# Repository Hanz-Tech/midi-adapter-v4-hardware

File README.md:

Buy it Here 

OR

# Disclaimer

You are free to:

Share — copy and redistribute the material in any medium or format

Adapt — remix, transform, and build upon the material

________________________________________

Attribution — You must give appropriate credit, provide a link to the license, and indicate if changes were made. You may do so in any reasonable manner, but not in any way that suggests the licensor endorses you or your use.

NonCommercial — You may not use the material for commercial purposes.

___________________________________________

THE HARDWARE IS PROVIDED "AS IS", WITHOUT WARRANTY OF ANY KIND, EXPRESS OR IMPLIED, INCLUDING BUT NOT LIMITED TO THE WARRANTIES OF MERCHANTABILITY, FITNESS FOR A PARTICULAR PURPOSE AND NONINFRINGEMENT. IN NO EVENT SHALL THE AUTHORS OR COPYRIGHT HOLDERS BE LIABLE FOR ANY CLAIM, DAMAGES OR OTHER LIABILITY, WHETHER IN AN ACTION OF CONTRACT, TORT OR OTHERWISE, ARISING FROM, OUT OF OR IN CONNECTION WITH THE HARDWARE OR THE USE OR OTHER DEALINGS IN THE HARDWARE.

_____________________________________________

# Overview

This repo contains both the CAD for the 3D printed cover for the Pocket Operator and the PCB schematic for the adapter. PCB is created using KiCad. Software can be found [here](https://github.com/PO-MIDI-Adapter/midi-adapter-software/tree/v2)

## For assmebly instruction please go to the [wiki](https://github.com/PO-MIDI-Adapter/midi-adapter-hardware/wiki)

# Photos

# BOM
<!-- 
1. 1 x PCB board
2. 1 x 3D printed cover (Found in the cad folder)
3. 2 x cover holders  (Found in the cad folder)
4. 25 x pogo pins [ebay](https://www.ebay.ca/itm/100pcs-9mm-Length-Spring-Loaded-Test-Probes-Pogo-Pins-Cusp-Spear-for-Testing/163156710143?ssPageName=STRK%3AMEBIDX%3AIT&_trksid=p2057872.m2749.l46252)
5. 1 x PJ320B 3.5MM Audio Jack (ebay)

In addition, you would need the following electronics from Digikey (bom.csv)

|Manufacturer Part Number|Manufacturer               |Digi-Key Part Number|Quantity|Description                     |Placement|
|------------------------|---------------------------|--------------------|--------|--------------------------------|---------|
|SN74HC125N              |Texas Instruments          |296-1572-5-ND       |1       |IC BUFFER NON-INVERT 6V 14DIP   |U2
|A 14-LC-TT              |Assmann WSW Components     |AE9989-ND           |1       |CONN IC DIP SOCKET 14POS TIN    |U2
|1-2199298-1             |TE Connectivity            |A120346-ND          |1       |CONN IC DIP SOCKET 6POS TIN     |U3
|H11L1M                  |ON Semiconductors          |H11L1-MQT-ND        |1       |OPTOISO 4.17KV OPN COLL 6DIP    |U3
|PRPC028SACN-RC          |Sullins Connector Solutions|S1131EC-28-ND       |2       |CONN HEADER VERT 28POS 2.54MM   |U1
|DEV-16771               |SparkFun Electronics       |1568-DEV-16771-ND   |1       |TEENSY 4.1 W/OUT HDRS K66 EVAL  |U1
|SDS-50J                 |CUI Inc.                   |CP-2350-ND          |2       |CONN RCPT FMALE DIN 5POS SOLDER |J29,J30
|CF14JT220R              |Stackpole Electronics Inc  |CF14JT220RCT-ND     |3       |RES 220 OHM 1/4W 5% AXIAL       |R2,R3,R7
|CF14JT10K0              |Stackpole Electronics Inc  |CF14JT10K0CT-ND     |1       |RES 10K OHM 1/4W 5% AXIAL       |R4
|CF14JT470R              |Stackpole Electronics Inc  |CF14JT470RTR-ND     |1       |RES 470 OHM 1/4W 5% AXIAL       |R8
|USB-A1HSW6              |On Shore Technology Incs   |ED2989-ND           |1       |USB-A Receptacle Connector 4 Pos|J19
|C315C104M5U5TA7303      |KEMET                      |399-9859-1-ND       |2       |CAP CER 0.1UF 50V Z5U RADIAL    |C2,C1
|PPTC041LFBN-RC          |Sullins Connector Solutions|S7002-ND            |1       |CONN HDR 4POS 0.1 TIN PCB       |J32
|1N914                   |ON Semiconductor           |1N914FS-ND          |1       |DIODE GEN PURP 100V 200MA DO35  |D1

Optional

|Manufacturer Part Number|Manufacturer               |Digi-Key Part Number|Quantity  |Description                   |Placement|
|------------------------|---------------------------|--------------------|--------|--------------------------------|---------|
|PPTC241LFBN-RC          |Sullins Connector Solutions|S7022-ND            |2       |CONN HDR 24POS 0.1 TIN PCB      |U1 -->

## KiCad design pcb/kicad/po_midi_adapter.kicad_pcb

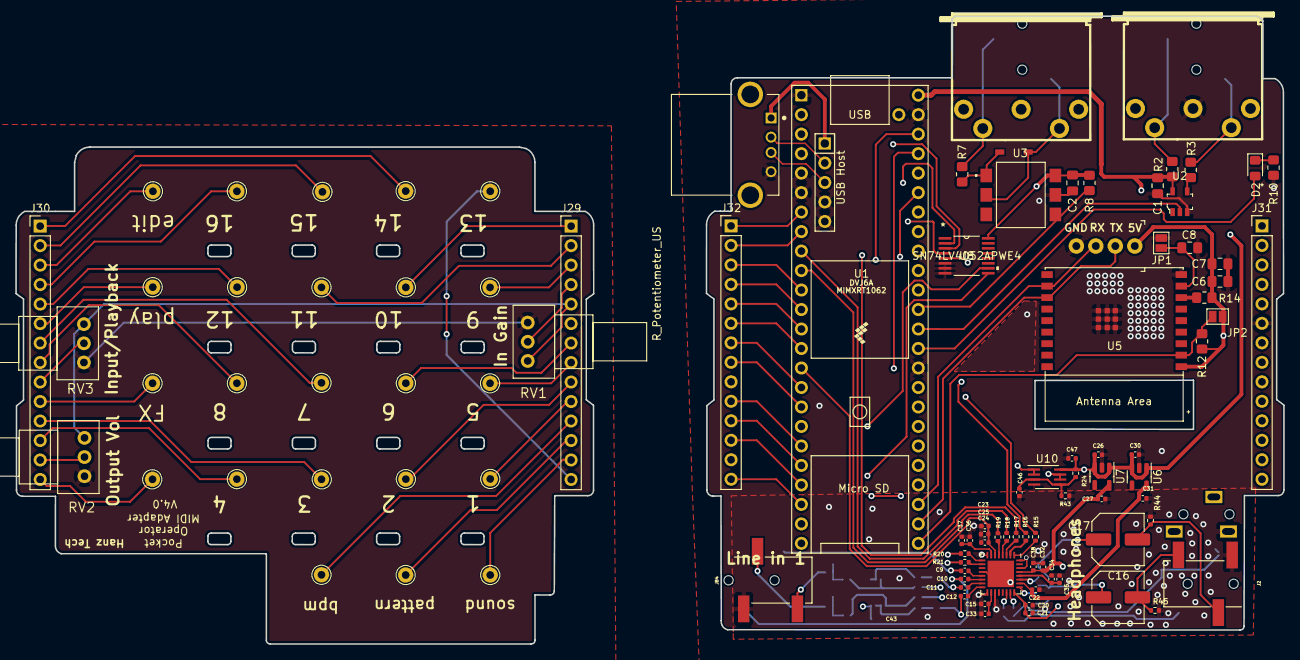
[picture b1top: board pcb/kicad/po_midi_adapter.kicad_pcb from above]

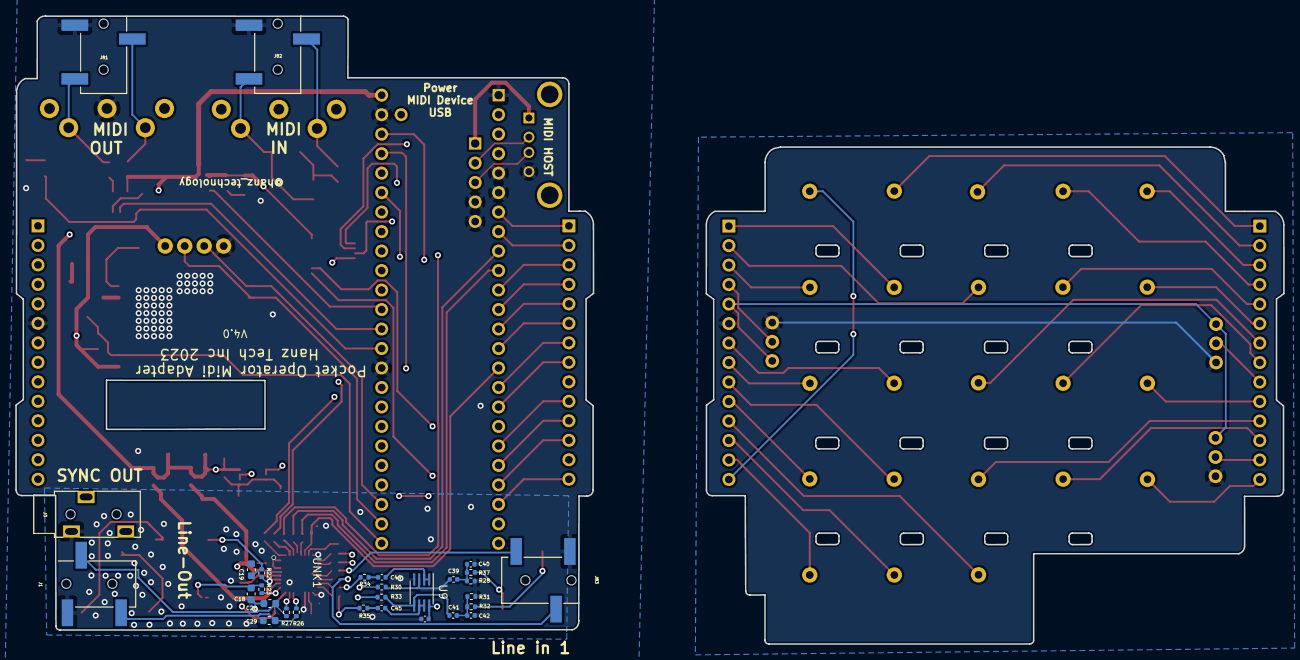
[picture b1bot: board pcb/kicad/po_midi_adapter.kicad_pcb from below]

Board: 4 copper layers, 165.2 x 81.8 mm, 127 parts (29 on the bottom side), 129 nets.

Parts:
C1, C2, C6, C8: 0.1uF; C_0805_2012Metric_Pad1.18x1.45mm_HandSolder
C7: 10uF; C_0805_2012Metric_Pad1.18x1.45mm_HandSolder
C9, C10, C11, C12: 2.2uF; C_0402_1005Metric
C15, C20, C23, C32, C34, C36, C46: 10uF; C_0402_1005Metric
C16, C17: 220uF; C_Elec_6.3x5.8
C18, C19, C28, C29: 4.7nF; C_0603_1608Metric
C21, C22, C24, C25, C33, C35, C37, C38, C39, C41: 0.1uF; C_0402_1005Metric
C26, C27, C30, C31: 1uF; C_0402_1005Metric
C40, C42: 470pF; C_0402_1005Metric
C43, C47: 100nF; C_0402_1005Metric
C44, C45: 4u7F; C_0402_1005Metric
D1: 1N4148; SOD-123
D2: LED; LED_0805_2012Metric_Pad1.15x1.40mm_HandSolder
J0: PJ-320B; 3.5mm_stereo_jack_PJ320B_THRU
J1, J2, J81, J82, J83, J84: PJ-320B; 3.5mm_stereo_jack_PJ320B
J4, J5, J6, J7, J8, J9, J10, J11, J12, J13, J14, J15, J16, J17, J18, J19, J20, J21, J22, J23, J24, J25, J28: Conn_01x01; Pin_D1.0mm_L10.0mm
J29, J30: Conn_01x14_Male; PinHeader_1x14_P2.54mm_Vertical
J31, J32: Conn_01x14_Female; PinHeader_1x14_P2.54mm_Vertical
J40: MIDI_1_IN; MIDI_DIN5_NO_ATTACHEMENT
J70: USB_A; TE_292303-1
J90: MIDI_1_OUT; MIDI_DIN5_NO_ATTACHEMENT
J99: 0022232041; PinHeader_1x4_P2.54mm_Drill1.02mm
JP1, JP2: Jumper; SolderJumper-2_P1.3mm_Open_Pad1.0x1.5mm
R2, R3, R7: 220; R_0805_2012Metric_Pad1.20x1.40mm_HandSolder
R8: 470; R_0805_2012Metric_Pad1.20x1.40mm_HandSolder
R10: 68; R_0805_2012Metric_Pad1.20x1.40mm_HandSolder
R12, R14: 10K; R_0805_2012Metric_Pad1.20x1.40mm_HandSolder
R15, R16, R17, R18, R19, R20, R21: 33R; R_0402_1005Metric
R22, R23, R26, R27, R34, R35: 1K; R_0402_1005Metric
R24, R43: 4K7; R_0402_1005Metric
R28, R30, R32, R33: 100K; R_0402_1005Metric
R31, R37: 100; R_0402_1005Metric
R44, R45: 10K; R_0402_1005Metric
RV1, RV2, RV3: R_Potentiometer_US; RES-ADJ-TH_RK09Y11L0001
U1: Teensy4.1; Teensy41_poma
U2: SN74LVC1G07DBVR; SOT-753
U3: H11L1S; IC_H11L1SM
U5: ESP32-C3-WROOM-02
U6: LP5907MFX-3.3; SOT-23-5
U7: LP5907MFX-1.8; SOT-23-5
U8: SN74LV4052APWE4
U9, U10: NE5532; TI-R-PDSO-G8
UNK1: TLV320AIC3204IRHBR; QFN-32-1EP_5x5mm_P0.5mm_EP3.45x3.45mm

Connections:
+1V8: C20.2, C21.2, C27.1, C32.2, C38.2, U7.5 (OUT), UNK1.24 (AVDD), UNK1.29 (DVDD)
/bottom/3.3V: C2.2, C6.1, C7.1, C23.1, C24.1, C25.1, J31.5, J99.1, JP2.1 (A), R8.1, R12.1, R14.2, U1.15 (3V3), U1.46 (3V3), U3.6 (VCC), U5.1 (3V3), U8.16 (VCC), UNK1.6 (IOVDD)
/bottom/5V: C1.2, C26.1, C30.1, C43.2, C47.2, R2.2, R24.1, U1.48 (VIN), U2.5 (VCC), U6.1 (IN), U6.3 (EN), U7.1 (IN), U7.3 (EN), U9.8 (V+), U10.8 (V+)
/bottom/ANALOG_IN: U1.4 (2_OUT2), U8.3 (2-COM)
/bottom/BCLK: R16.2, U1.43 (21_A7_RX5_BCLK1)
/bottom/DIN: R18.2, U1.9 (7_RX2_OUT1A)
/bottom/DOUT: R19.2, U1.10 (8_TX2_IN1)
/bottom/ESP32_EN: JP2.2 (B), R12.2, U1.25 (33_MCLK2), U5.2 (EN/CHIP_PU)
/bottom/GIPO_PATTERN: J31.12, U1.30 (38_CS1_IN1)
/bottom/GND: C1.1, C2.1, C6.2, C7.2, C8.2, C15.1, C18.1, C19.2, C20.1, C21.1, C22.1, C23.2, C24.2, C25.2, C26.2, C27.2, C28.1, C29.1, C30.2, C31.2, C32.1, C33.1, C34.1, C35.1, C36.1, C37.1, C38.1, C40.2, C42.2, C43.1, C46.1, C47.1, J0.1, J1.1, J2.1, J31.6, J70.4 (GND), J81.1, J82.1, J83.1, J84.1, J90.2, J99.4, JP1.1 (A), R10.2, R28.1, R32.1, R43.2, R44.2, R45.1, U1.1 (GND), U1.5 (3_LRCLK2), U1.6 (4_BCLK2), U1.34 (GND), U1.47 (GND), U1.58 (GND), U1.59 (GND), U2.3 (GND), U3.5 (GND), U5.9 (GND), U5.19 (GND), U6.2 (GND), U7.2 (GND), U8.6 (INH), U8.7 (GND), U8.8 (GND), U9.4 (V-), U10.4 (V-), UNK1.8 (SCLK/MFP3), UNK1.12 (SPI_SELECT), UNK1.17 (AVSS), UNK1.19 (MICBIAS), UNK1.30 (LDO_SELECT), UNK1.32 (GPIO/MFP5), UNK1.33 (EP)
/bottom/GPIO_1: J31.10, U1.32 (40_A16)
/bottom/GPIO_2: J31.9, U1.33 (41_A17)
/bottom/GPIO_3: J32.11, U1.20 (28_RX7)
/bottom/GPIO_4: J32.12, U1.21 (29_TX7)
/bottom/GPIO_5: J31.8, U1.38 (16_A2_RX4_SCL1)
/bottom/GPIO_6: J31.7, U1.39 (17_A3_TX4_SDA1)
/bottom/GPIO_7: J32.7, U1.16 (24_A10_TX6_SCL2)
/bottom/GPIO_8: J32.8, U1.17 (25_A11_RX6_SDA2)
/bottom/GPIO_9: J31.3, U1.44 (22_A8_CTX1)
/bottom/GPIO_10: J31.1, U1.2 (0_RX1_CRX2_CS1)
/bottom/GPIO_11: J31.2, U1.3 (1_TX1_CTX2_MISO1)
/bottom/GPIO_12: J32.5, U1.13 (11_MOSI_CTX1)
/bottom/GPIO_13: J31.14, U1.28 (36_CS)
/bottom/GPIO_14: J32.1, U1.7 (5_IN2)
/bottom/GPIO_15: J32.2, U1.8 (6_OUT1D)
/bottom/GPIO_16: J32.4, U1.12 (10_CS_MQSR)
/bottom/GPIO_BPM: J31.11, U1.31 (39_MISO1_OUT1A)
/bottom/GPIO_FX: J32.10, U1.19 (27_A13_SCK1)
/bottom/GPIO_PLAY: J32.6, U1.14 (12_MISO_MQSL)
/bottom/GPIO_SOUND: J31.13, U1.29 (37_CS)
/bottom/GPIO_SPECIAL: J32.14, U1.22 (30_CRX3)
/bottom/GPIO_WRITE: J32.3, U1.11 (9_OUT1C)
/bottom/HPL: C16.2, J2.2, R45.2
/bottom/HPR: C17.2, J2.3, R44.1
/bottom/HP_3V3: C22.2, C31.1, U6.5 (OUT), UNK1.26 (LDOIN/HPVDD)
/bottom/H_USB_5V: J70.1 (VBUS), U1.55 (5V)
/bottom/H_USB_D+: J70.3 (D+), U1.57 (D+)
/bottom/H_USB_D-: J70.2 (D-), U1.56 (D-)
/bottom/LOL: C29.2, J1.2, R26.2
/bottom/LOR: C28.2, J1.3, R27.2
/bottom/MCLK: R15.2, U1.45 (23_A9_CRX1_MCLK1)
/bottom/MIDI_1_BUF_OUT: R3.2, U2.4 (Y)
/bottom/MIDI_1_IN: R8.2, U1.37 (15_A1_RX3_SPDIF_IN), U3.4 (VO)
/bottom/MIDI_1_OUT: U1.36 (14_A0_TX3_SPDIF_OUT), U2.2 (A)
/bottom/MIDI_IN_EXT: J99.2, U1.26 (34_RX8), U5.12 (GPIO21/U0TXD)
/bottom/MIDI_OUT_EXT: J99.3, U1.27 (35_TX8), U5.11 (GPIO20/U0RXD)
/bottom/POT_GAIN_IN: J31.4, U8.5 (2Y1)
/bottom/POT_INPUT_PLAY_MIX: J32.9, U8.2 (2Y2)
/bottom/POT_VOL_OUT: J32.13, U8.4 (2Y3)
/bottom/SCL: R20.2, U1.41 (19_A5_SCL)
/bottom/SDA: R21.2, U1.40 (18_A4_SDA)
/bottom/SELECT_A: U1.18 (26_A12_MOSI1), U8.10 (A)
/bottom/SELECT_B: U1.23 (31_CTX3), U8.9 (B)
/bottom/SYNC_OUT: J0.2, U1.24 (32_OUT1B)
/bottom/WCLK: R17.2, U1.42 (20_A6_TX5_LRCLK1)
/bottom/codec_in_2_l: C11.1, R34.2
/bottom/codec_in_2_r: C12.1, R35.2
/bottom/in2_l: J84.2, R37.1
/bottom/in2_r: J84.3, R31.1
/bottom/vbias_in_l: R30.2, U10.1, U10.2 (-)
/bottom/vbias_in_r: R33.2, U10.6 (-), U10.7
/top/3.3V: J29.5, RV1.1, RV2.1, RV3.1
/top/GIPO_PATTERN: J20.1, J29.12
/top/GND: J29.6, RV1.3, RV2.3, RV3.3
/top/GPIO_1: J6.1, J29.10
/top/GPIO_2: J5.1, J29.9
/top/GPIO_3: J4.1, J30.11
/top/GPIO_4: J22.1, J30.12
/top/GPIO_5: J8.1, J29.8
/top/GPIO_6: J9.1, J29.7
/top/GPIO_7: J10.1, J30.7
/top/GPIO_8: J11.1, J30.8
/top/GPIO_9: J12.1, J29.3
/top/GPIO_10: J13.1, J29.1
/top/GPIO_11: J28.1, J29.2
/top/GPIO_12: J14.1, J30.5
/top/GPIO_13: J17.1, J29.14
/top/GPIO_14: J16.1, J30.1
/top/GPIO_15: J7.1, J30.2
/top/GPIO_16: J25.1, J30.4
/top/GPIO_BPM: J21.1, J29.11
/top/GPIO_FX: J23.1, J30.10
/top/GPIO_PLAY: J24.1, J30.6
/top/GPIO_SOUND: J19.1, J29.13
/top/GPIO_SPECIAL: J15.1, J30.14
/top/GPIO_WRITE: J18.1, J30.3
/top/POT_GAIN_IN: J29.4, RV1.2
/top/POT_INPUT_PLAY_MIX: J30.9, RV3.2
/top/POT_VOL_OUT: J30.13, RV2.2
unnamed: C8.1, JP1.2 (B), U5.8 (GPIO9)
unnamed: C9.1, J83.2
unnamed: C9.2, UNK1.13 (IN1_L)
unnamed: C10.1, J83.3
unnamed: C10.2, UNK1.14 (IN1_R)
unnamed: C11.2, UNK1.15 (IN2_L)
unnamed: C12.2, UNK1.16 (IN2_R)
unnamed: C15.2, C33.2, UNK1.18 (REF)
unnamed: C16.1, C18.2, R23.2
unnamed: C17.1, C19.1, R22.2
unnamed: C34.2, C35.2, UNK1.28 (DVSS)
unnamed: C36.2, C37.2, UNK1.7 (IOVSS)
unnamed: C39.1, R30.1, U9.3 (+)
unnamed: C39.2, C40.1, R28.2, R37.2
unnamed: C41.1, R33.1, U9.5 (+)
unnamed: C41.2, C42.1, R31.2, R32.2
unnamed: C44.1, R34.1
unnamed: C44.2, U9.1, U9.2 (-)
unnamed: C45.1, R35.1
unnamed: C45.2, U9.6 (-), U9.7
unnamed: C46.2, R24.2, R43.1, U10.3 (+), U10.5 (+)
unnamed: D1.1 (K), R7.2, U3.1
unnamed: D1.2 (A), J40.5, J82.2, U3.2
unnamed: D2.1 (K), R10.1
unnamed: D2.2 (A), U1.35 (13_SCK_LED)
unnamed: J40.4, J82.3, R7.1
unnamed: J81.2, J90.5, R3.1
unnamed: J81.3, J90.4, R2.1
unnamed: R14.1, U5.7 (GPIO8)
unnamed: R15.1, UNK1.1 (MCLK)
unnamed: R16.1, UNK1.2 (BCLK)
unnamed: R17.1, UNK1.3 (WCLK)
unnamed: R18.1, UNK1.4 (DIN/MFP1)
unnamed: R19.1, UNK1.5 (DOUT/MFP2)
unnamed: R20.1, UNK1.9 (SCL/SS#)
unnamed: R21.1, UNK1.10 (SDA/MOSI)
unnamed: R22.1, UNK1.27 (HPR)
unnamed: R23.1, UNK1.25 (HPL)
unnamed: R26.1, UNK1.22 (LOL)
unnamed: R27.1, UNK1.23 (LOR)

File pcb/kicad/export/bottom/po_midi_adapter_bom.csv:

Comment	Designator	Footprint	LCSC
0.1uF	C1,C2,C6,C8	Capacitor_SMD:C_0805_2012Metric_Pad1.18x1.45mm_HandSolder	C28233
10uF	C15,C20,C23,C32,C34,C36	Capacitor_SMD:C_0402_1005Metric	C105884
1uF	C16,C17,C26,C27,C30,C31	Capacitor_SMD:C_0402_1005Metric	C326568
47uF	C18,C19,C28,C29	Capacitor_SMD:C_0805_2012Metric	C16780 
0.1uF	C21,C22,C24,C25,C33,C35,C37,C38	Capacitor_SMD:C_0402_1005Metric	C49678
10uF	C7	Capacitor_SMD:C_0805_2012Metric_Pad1.18x1.45mm_HandSolder	C440198
2.2uF	C9,C10,C11,C12	Capacitor_SMD:C_0402_1005Metric	C12503
1N4148	D1	poma:SOD-123	C908248
LED	D2	LED_SMD:LED_0805_2012Metric_Pad1.15x1.40mm_HandSolder	C401117
PJ-320B	J1,J2,J81,J82	jacks:3.5mm_stereo_jack_PJ320B	C707224
Conn_01x14_Female	J31,J32	Connector_PinHeader_2.54mm:PinHeader_1x14_P2.54mm_Vertical	C124407
PJ-320B	J83,J84	poma:3.5mm_stereo_jack_PJ320B	C707224
68	R10	Resistor_SMD:R_0805_2012Metric_Pad1.20x1.40mm_HandSolder	C17784 
10K	R12,R14	Resistor_SMD:R_0805_2012Metric_Pad1.20x1.40mm_HandSolder	C17414 
33R	R15,R16,R17,R18,R19,R20,R21	Resistor_SMD:R_0402_1005Metric	C25105
220	R2,R3,R7	Resistor_SMD:R_0805_2012Metric_Pad1.20x1.40mm_HandSolder	C17557 
6.8K	R22,R23	Resistor_SMD:R_0402_1005Metric	C25917
10K	R24,R25	Resistor_SMD:R_0402_1005Metric	C25744
100	R26,R27	Resistor_SMD:R_0402_1005Metric	C25076
470	R8	Resistor_SMD:R_0805_2012Metric_Pad1.20x1.40mm_HandSolder	C17710 
R_Potentiometer_US	RV1,RV2,RV3	poma:RES-ADJ-TH_RK09Y11L0001	C470717
SN74LVC1G07DBVR	U2	digikey-footprints:SOT-753	C7829
H11L1S	U3	poma:IC_H11L1SM	C78589 
ESP32-C3-WROOM-02	U5	Espressif:ESP32-C3-WROOM-02	C2934560
LP5907MFX-3.3	U6	Package_TO_SOT_SMD:SOT-23-5	C80670
LP5907MFX-1.8	U7	Package_TO_SOT_SMD:SOT-23-5	C92498
SN74LV4052APWE4	U8	poma:SN74LV4052APWE4	C8142
TLV320AIC3204IRHBR	UNK1	Package_DFN_QFN:QFN-32-1EP_5x5mm_P0.5mm_EP3.45x3.45mm	C24109

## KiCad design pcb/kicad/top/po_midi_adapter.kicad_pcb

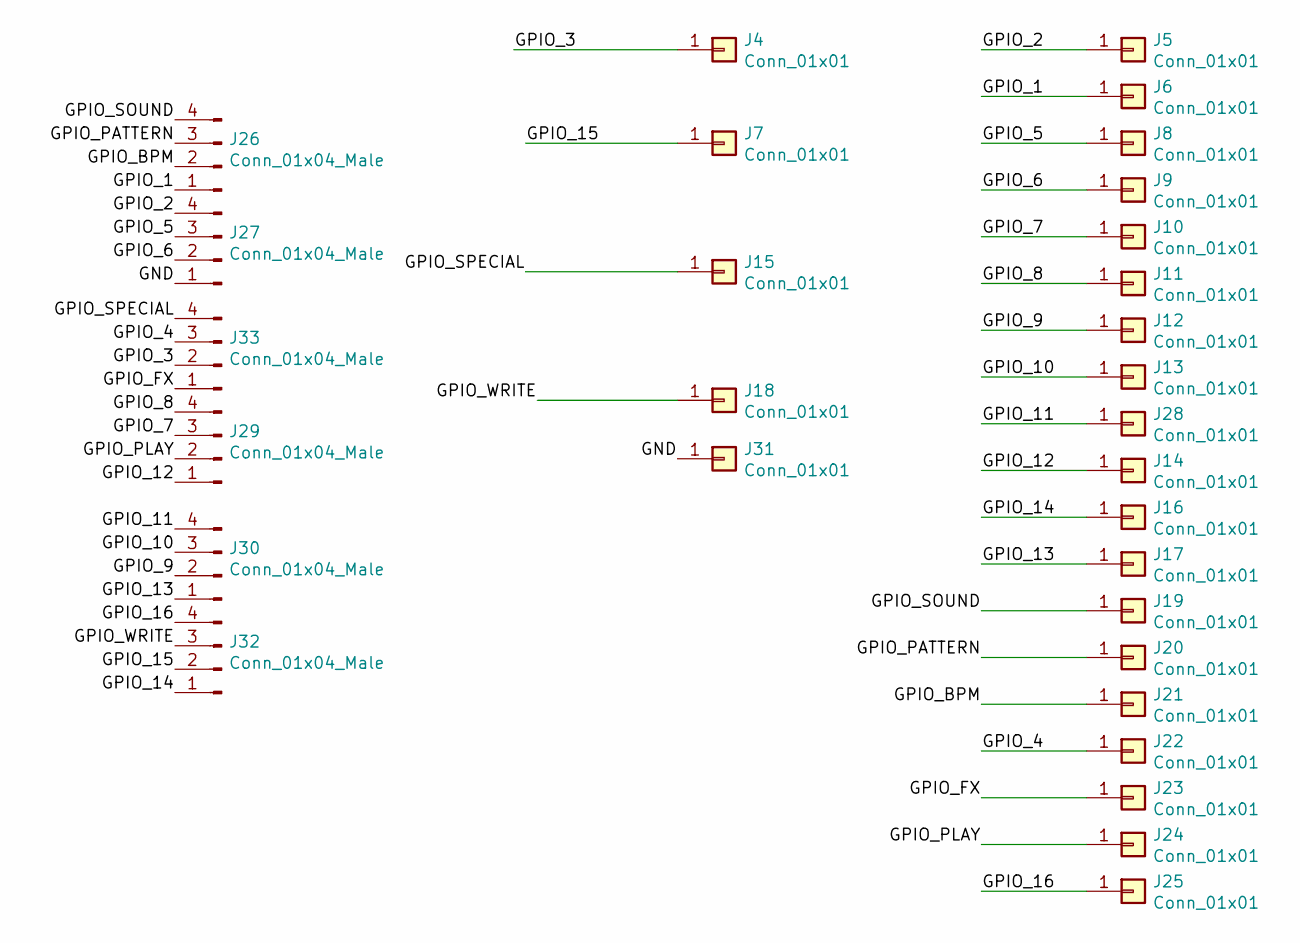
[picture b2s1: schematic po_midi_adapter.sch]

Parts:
J4, J5, J6, J7, J8, J9, J10, J11, J12, J13, J14, J15, J16, J17, J19, J20, J21, J22, J23, J24, J25, J28: Conn_01x01; Pin_D1.0mm_L10.0mm_po
J18, J31: Conn_01x01; Pin_D1.0mm_L10.0mm
J26, J27, J29, J30, J32, J33: Conn_01x04_Male; PinSocket_1x04_P2.54mm_Vertical

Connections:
/GND: J27.1, J31.1
/GPIO_1: J6.1, J26.1
/GPIO_2: J5.1, J27.4
/GPIO_3: J4.1, J33.2
/GPIO_4: J22.1, J33.3
/GPIO_5: J8.1, J27.3
/GPIO_6: J9.1, J27.2
/GPIO_7: J10.1, J29.3
/GPIO_8: J11.1, J29.4
/GPIO_9: J12.1, J30.2
/GPIO_10: J13.1, J30.3
/GPIO_11: J28.1, J30.4
/GPIO_12: J14.1, J29.1
/GPIO_13: J17.1, J30.1
/GPIO_14: J16.1, J32.1
/GPIO_15: J7.1, J32.2
/GPIO_16: J25.1, J32.4
/GPIO_BPM: J21.1, J26.2
/GPIO_FX: J23.1, J33.1
/GPIO_PATTERN: J20.1, J26.3
/GPIO_PLAY: J24.1, J29.2
/GPIO_SOUND: J19.1, J26.4
/GPIO_SPECIAL: J15.1, J33.4
/GPIO_WRITE: J18.1, J32.3

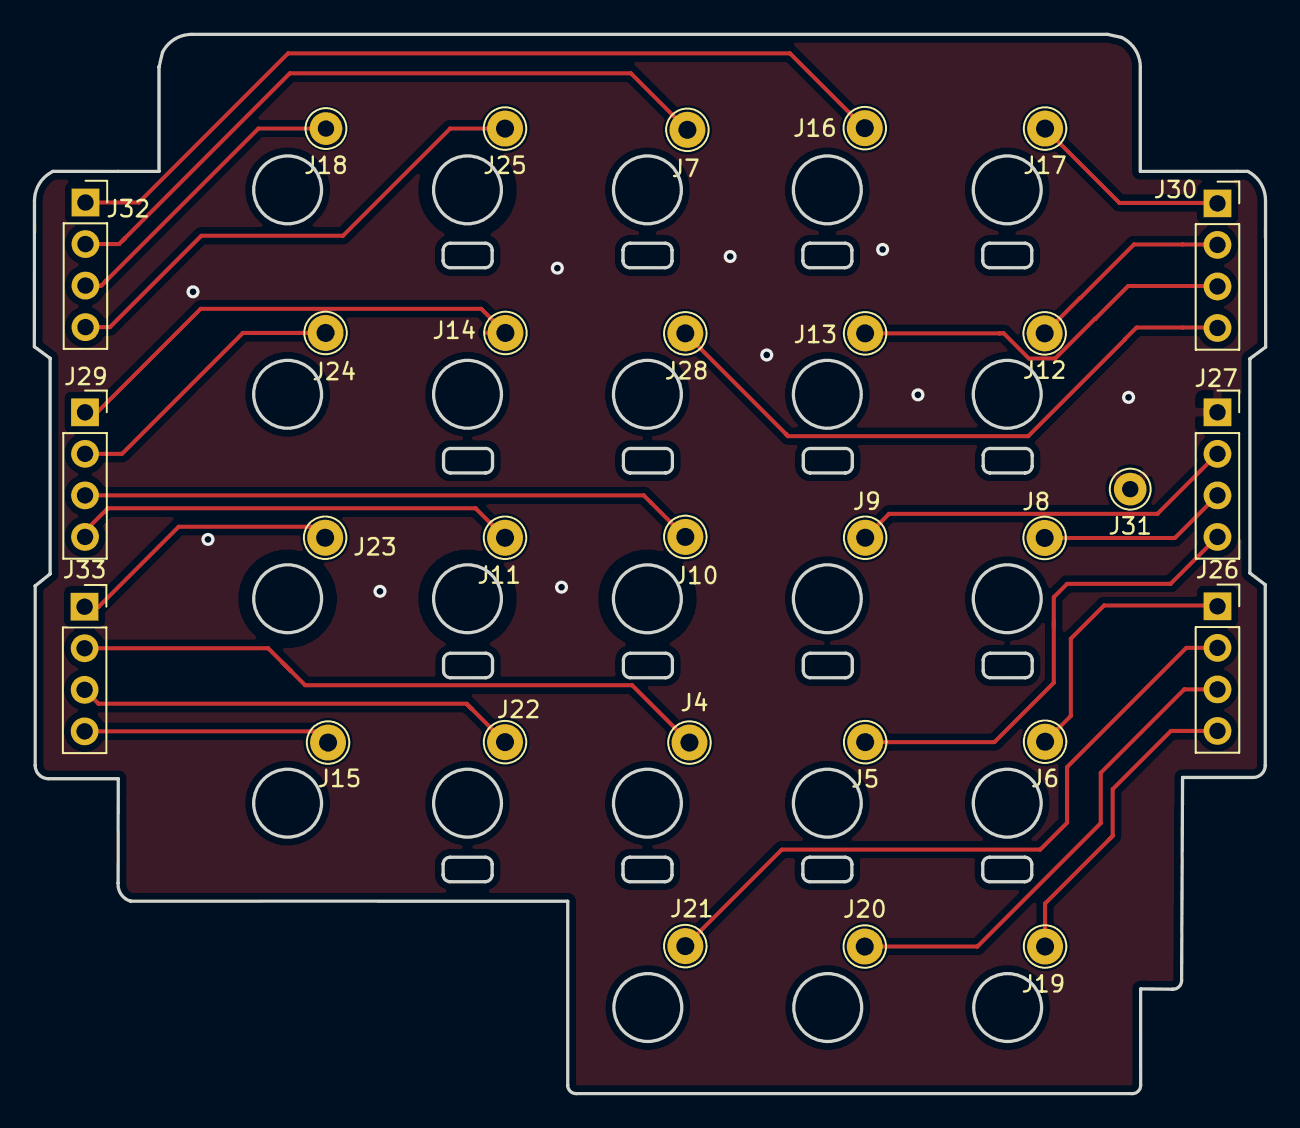
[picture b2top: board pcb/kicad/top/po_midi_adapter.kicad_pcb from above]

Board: 2 copper layers, 75.3 x 64.8 mm, 30 parts (0 on the bottom side), 24 nets.

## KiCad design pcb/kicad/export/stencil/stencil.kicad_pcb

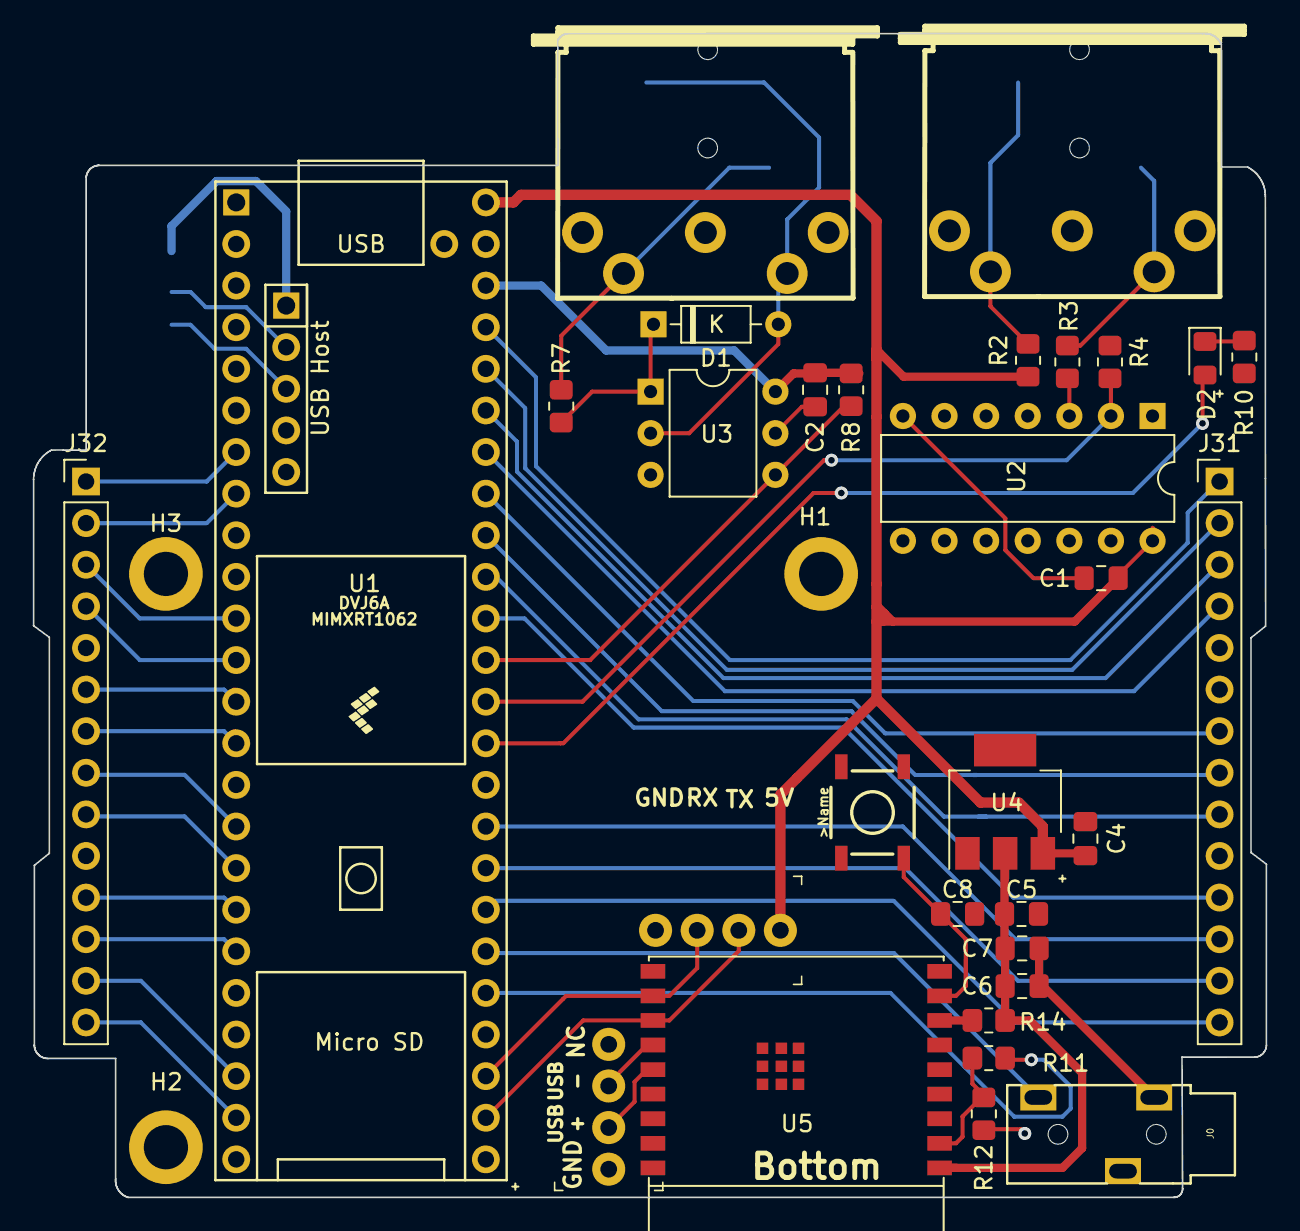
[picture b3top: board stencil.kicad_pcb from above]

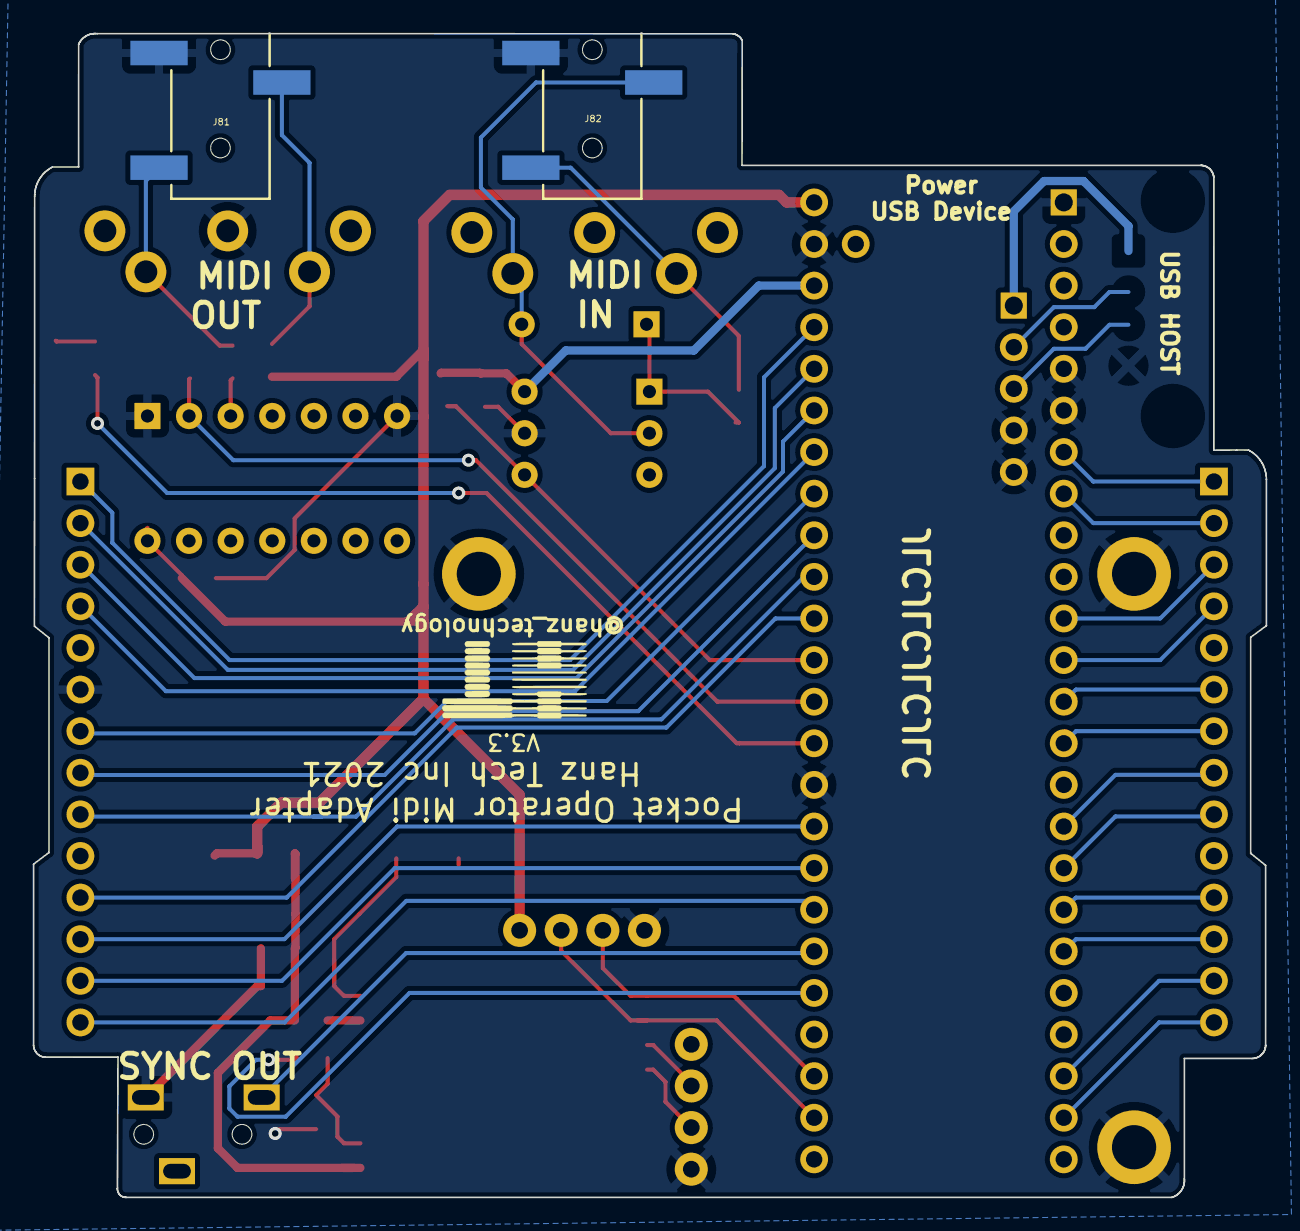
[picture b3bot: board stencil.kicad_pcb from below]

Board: 2 copper layers, 75.3 x 71.0 mm, 36 parts (2 on the bottom side), 46 nets.

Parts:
C1, C2, C6, C8: 0.1uF; C_0805_2012Metric_Pad1.18x1.45mm_HandSolder
C4: 1uF; C_0805_2012Metric_Pad1.18x1.45mm_HandSolder
C5, C7: 10uF; C_0805_2012Metric_Pad1.18x1.45mm_HandSolder
D1: 1N914; D_DO-35_SOD27_P7.62mm_Horizontal
D2: LED; LED_0805_2012Metric_Pad1.15x1.40mm_HandSolder
H1, H2, H3: MountingHole_Pad; MountingHole_2.7mm_M2.5_ISO7380_Pad
J0: PJ-320B; 3.5mm_stereo_jack_PJ320B_THRU
J31, J32: Conn_01x14_Female; PinHeader_1x14_P2.54mm_Vertical
J40: MIDI_1_IN; MIDI_DIN5_NO_ATTACHEMENT
J81, J82: PJ-320B; 3.5mm_stereo_jack_PJ320B
J90: MIDI_1_OUT; MIDI_DIN5_NO_ATTACHEMENT
J96, J99: 0022232041; PinHeader_1x4_P2.54mm_Drill1.02mm
R2, R3, R7: 220; R_0805_2012Metric_Pad1.20x1.40mm_HandSolder
R4, R11, R12, R14: 10K; R_0805_2012Metric_Pad1.20x1.40mm_HandSolder
R8: 470; R_0805_2012Metric_Pad1.20x1.40mm_HandSolder
R10: 50; R_0805_2012Metric_Pad1.20x1.40mm_HandSolder
S1: MOMENTARY-SWITCH-SPST-SMD-5.2MM; TACTILE_SWITCH_SMD_5.2MM
U1: Teensy4.1; Teensy41_poma
U2: SN74HC125N; DIP-14_W7.62mm
U3: H11L1M; DIP-6_W7.62mm
U4: LM1117-3.3; SOT-223
U5: ESP32-C3-WROOM-02

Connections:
Board_0-/bottom/3.3V: C2.2, R8.1, U1.46 (3V3), U3.6 (VCC)
Board_0-/bottom/3.3V_ESP32: C5.1, C6.1, C7.1, R14.2, U4.2 (VO), U5.1 (3V3)
Board_0-/bottom/5V: C1.2, C4.1, J99.1, R2.2, U1.48 (VIN), U2.14 (VCC), U4.3 (VI)
Board_0-/bottom/ESP32_EN: R11.2, U1.29 (37_CS)
Board_0-/bottom/GIPO_PATTERN: J31.13, U1.32 (40_A16)
Board_0-/bottom/GND: C1.1, C2.1, C4.2, C5.2, C6.2, C7.2, C8.2, H1.1, H2.1, H3.1, J0.1, J31.6, J81.1, J82.1, J90.2, J96.1, J99.4, R4.1, R10.2, R12.1, S1.1, U1.1 (GND), U1.5 (3_LRCLK2), U1.6 (4_BCLK2), U1.34 (GND), U1.47 (GND), U1.58 (GND), U1.59 (GND), U2.1 (1~OE), U2.7 (GND), U3.5 (GND), U4.1 (GND), U5.9 (GND), U5.19 (GND)
Board_0-/bottom/GPIO_1: J31.11, U1.38 (16_A2_RX4_SCL1)
Board_0-/bottom/GPIO_2: J31.9, U1.39 (17_A3_TX4_SDA1)
Board_0-/bottom/GPIO_3: J32.12, U1.19 (27_A13_SCK1)
Board_0-/bottom/GPIO_4: J32.13, U1.22 (30_CRX3)
Board_0-/bottom/GPIO_5: J31.8, U1.40 (18_A4_SDA)
Board_0-/bottom/GPIO_6: J31.7, U1.41 (19_A5_SCL)
Board_0-/bottom/GPIO_7: J32.8, U1.16 (24_A10_TX6_SCL2)
Board_0-/bottom/GPIO_8: J32.9, U1.17 (25_A11_RX6_SDA2)
Board_0-/bottom/GPIO_9: J31.2, U1.44 (22_A8_CTX1)
Board_0-/bottom/GPIO_10: J31.3, U1.43 (21_A7_RX5_BCLK1)
Board_0-/bottom/GPIO_11: J31.4, U1.42 (20_A6_TX5_LRCLK1)
Board_0-/bottom/GPIO_12: J32.6, U1.13 (11_MOSI_CTX1)
Board_0-/bottom/GPIO_13: J31.1, U1.45 (23_A9_CRX1_MCLK1)
Board_0-/bottom/GPIO_14: J32.1, U1.7 (5_IN2)
Board_0-/bottom/GPIO_15: J32.2, U1.8 (6_OUT1D)
Board_0-/bottom/GPIO_16: J32.4, U1.12 (10_CS_MQSR)
Board_0-/bottom/GPIO_BPM: J31.12, U1.33 (41_A17)
Board_0-/bottom/GPIO_FX: J32.11, U1.18 (26_A12_MOSI1)
Board_0-/bottom/GPIO_PLAY: J32.7, U1.14 (12_MISO_MQSL)
Board_0-/bottom/GPIO_SOUND: J31.14, U1.31 (39_MISO1_OUT1A)
Board_0-/bottom/GPIO_SPECIAL: J32.14, U1.23 (31_CTX3)
Board_0-/bottom/GPIO_WRITE: J32.3, U1.11 (9_OUT1C)
Board_0-/bottom/MIDI_1_BUF_OUT: R3.2, U2.3 (1Y)
Board_0-/bottom/MIDI_1_IN: R8.2, U1.37 (15_A1_RX3_SPDIF_IN), U3.4 (VO)
Board_0-/bottom/MIDI_1_OUT: R4.2, U1.36 (14_A0_TX3_SPDIF_OUT), U2.2 (1A)
Board_0-/bottom/MIDI_IN_EXT: J99.2, U1.26 (34_RX8), U5.12 (GPIO21/U0TXD)
Board_0-/bottom/MIDI_OUT_EXT: J99.3, U1.27 (35_TX8), U5.11 (GPIO20/U0RXD)
Board_0-/bottom/SYNC_OUT: J0.2, U1.30 (38_CS1_IN1)
Board_0-Net-(C8-Pad1): C8.1, S1.3 (2), U5.8 (GPIO9)
Board_0-Net-(D1-Pad1): D1.1 (K), R7.2, U3.1
Board_0-Net-(D1-Pad2): D1.2 (A), J40.5, J82.3, U3.2
Board_0-Net-(D2-Pad1): D2.1 (K), R10.1
Board_0-Net-(D2-Pad2): D2.2 (A), U1.35 (13_SCK_LED)
Board_0-Net-(J40-Pad4): J40.4, J82.2, R7.1
Board_0-Net-(J81-Pad2): J81.2, J90.5, R3.1
Board_0-Net-(J81-Pad3): J81.3, J90.4, R2.1
Board_0-Net-(J96-Pad2): J96.2, U5.14 (GPIO19/USB_D+)
Board_0-Net-(J96-Pad3): J96.3, U5.13 (GPIO18/USB_D-)
Board_0-Net-(R11-Pad1): R11.1, R12.2, U5.2 (EN/CHIP_PU)
Board_0-Net-(R14-Pad1): R14.1, U5.7 (GPIO8)

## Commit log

2021-10-23 split to top and bottom board
2021-12-05 switched to hierarchical design
2021-12-06 update board with logo
2021-12-06 cleanup
2021-12-09 Added esp32 c3 for MIDI BLE
2021-12-12 fixed bottom board LDO footprint
2021-12-22 updated bom, removed old photo, added render
2022-01-05 fixed power supply footprint
2022-01-11 fixed strapping pin 8
2022-01-11 version bump to 3.1
2022-01-20 bump to v3.1, upgrade to kicad v6
2022-02-23 v3.2 : added midi trs, connected ESP32 EN pin to Teensy
2022-03-06 update to version 3.3, include trs midi, esp32-enable pin
2022-05-29 update to 3.4, ready for production
2022-06-17 cleanup 3d models
2023-01-10 added new codec chip tlc320aic3204
2023-01-11 shifting pins
2023-01-12 fixed routing for esp32
2023-01-13 started codec placement
2023-01-16 codec layout
2023-02-01 update bottom board
2023-02-02 update board
2023-02-04 add multiplexer
2023-02-04 finished routing
2023-02-04 Fix DRC errors
2023-02-04 add missing jack
2023-02-04 small cleanup
2023-02-07 submitted order 4.0
2023-02-07 Remove old csv
2023-04-08 added buffers to output and input
2023-04-08 final version 4.0
2023-04-14 finished placing components

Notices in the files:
README.md:
License: CC BY-NC 4.0
parts and their libraries:
Copyright 2021 Accelerated Designs. All rights reserved.
